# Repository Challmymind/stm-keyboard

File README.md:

First iteration of my 30% keyboard PCB. </br>
Newest board with fixes [here](https://github.com/Challmymind/anvil_pcb).

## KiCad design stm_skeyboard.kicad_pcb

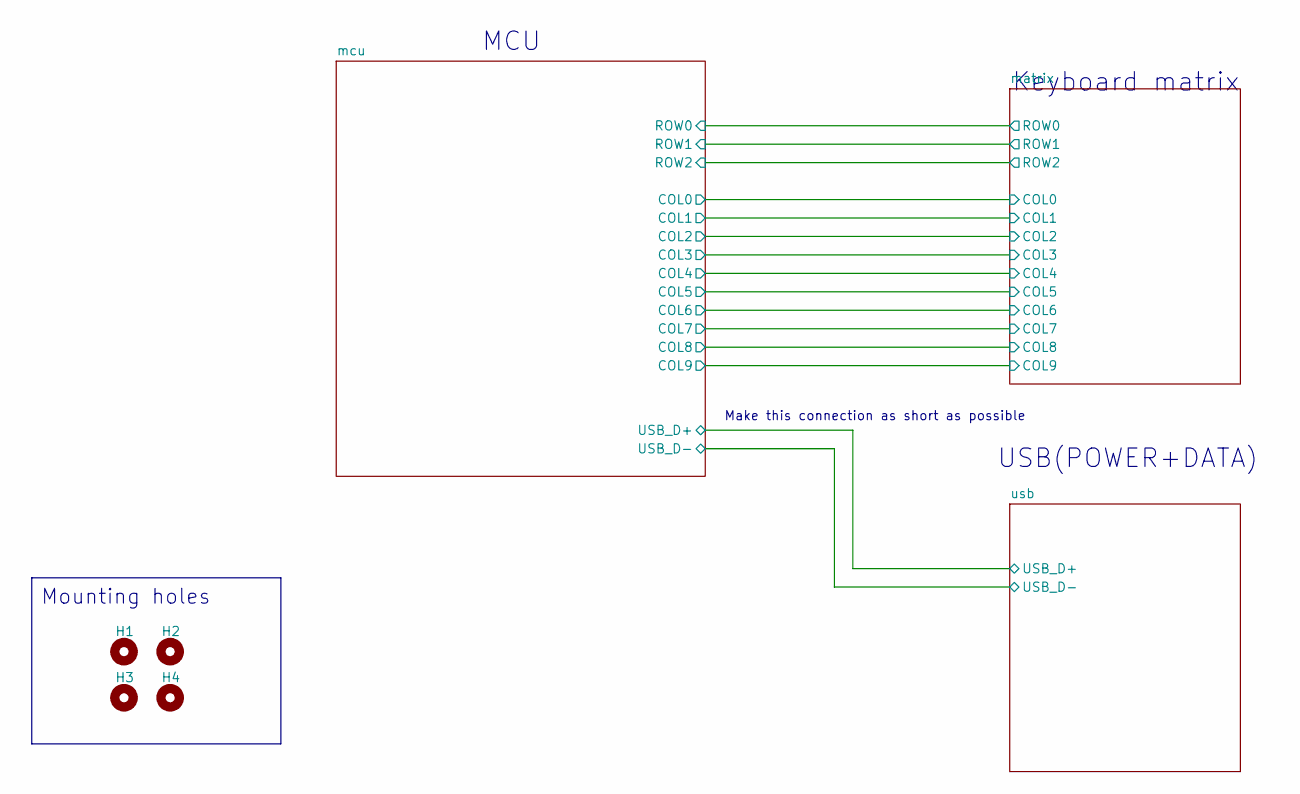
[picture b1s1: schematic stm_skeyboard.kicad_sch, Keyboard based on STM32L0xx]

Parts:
H1, H2, H3, H4: MountingHole; MountingHole_2.1mm

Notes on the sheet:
MCU
Keyboard matrix
Make this connection as short as possible
Mounting holes
USB(POWER+DATA)

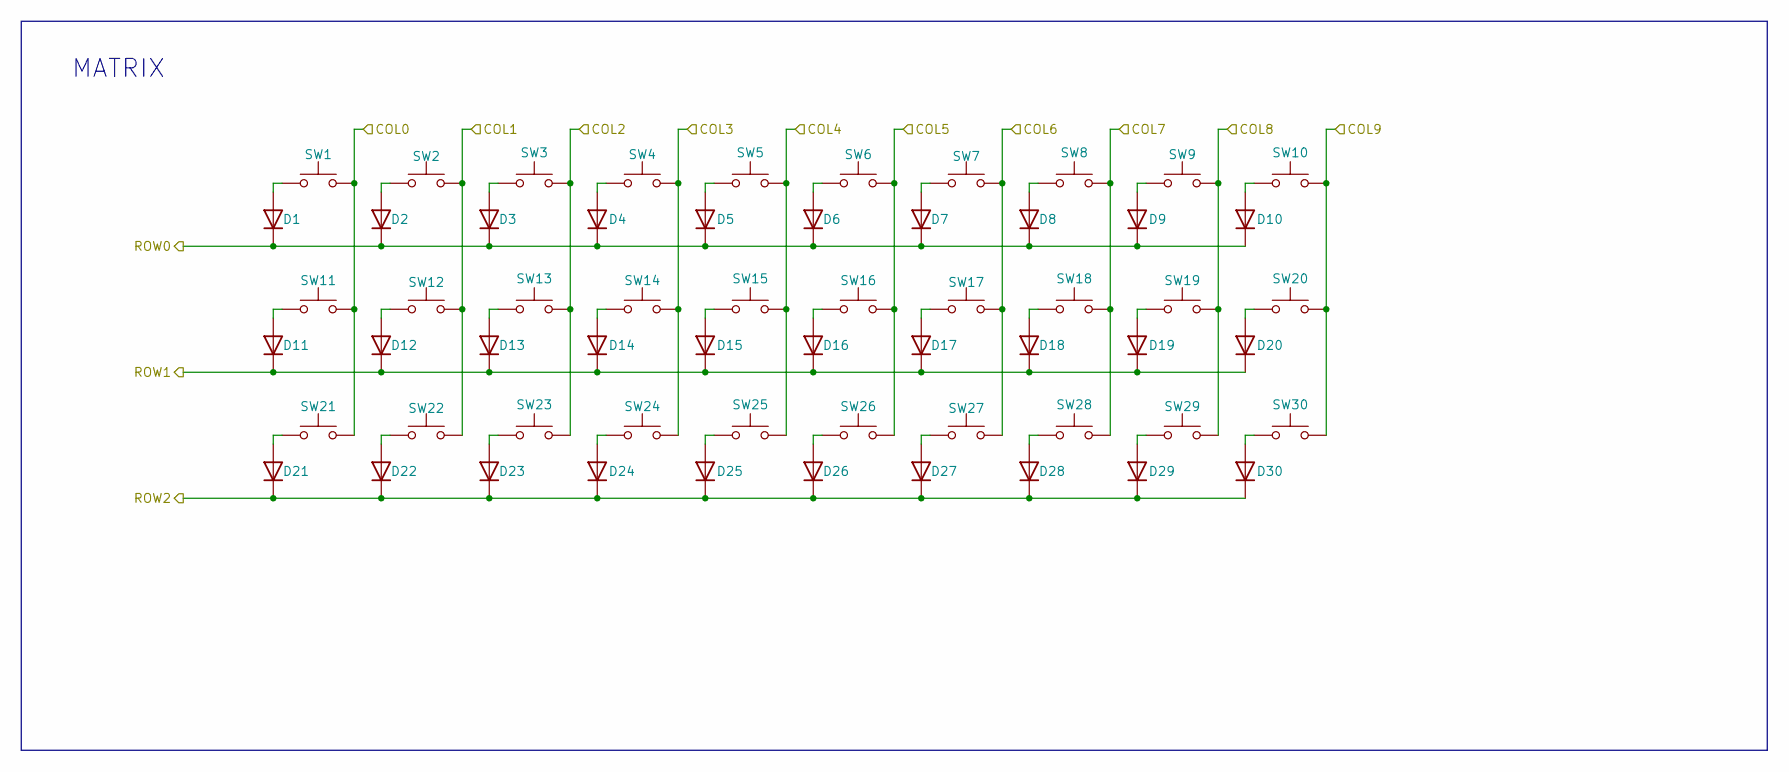
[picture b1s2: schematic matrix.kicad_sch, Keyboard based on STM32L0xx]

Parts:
D1, D2, D3, D4, D5, D6, D7, D8, D9, D10, D11, D12, D13, D14, D15, D16, D17, D18, D19, D20, D21, D22, D23, D24, D25, D26, D27, D28, D29, D30: D; D_SOD-123
SW1, SW2, SW3, SW4, SW5, SW6, SW7, SW8, SW9, SW10, SW11, SW12, SW13, SW14, SW15, SW16, SW17, SW18, SW19, SW20, SW21, SW22, SW23, SW24, SW25, SW26, SW27, SW28, SW29, SW30: SW_Push; SW_Cherry_MX_1.00u_PCB_no_support_stems

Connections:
/matrix/COL0: SW1.2, SW11.2, SW21.2; also elsewhere on the board
/matrix/COL1: SW2.2, SW12.2, SW22.2; also elsewhere on the board
/matrix/COL2: SW3.2, SW13.2, SW23.2; also elsewhere on the board
/matrix/COL3: SW4.2, SW14.2, SW24.2; also elsewhere on the board
/matrix/COL4: SW5.2, SW15.2, SW25.2; also elsewhere on the board
/matrix/COL5: SW6.2, SW16.2, SW26.2; also elsewhere on the board
/matrix/COL6: SW7.2, SW17.2, SW27.2; also elsewhere on the board
/matrix/COL7: SW8.2, SW18.2, SW28.2; also elsewhere on the board
/matrix/COL8: SW9.2, SW19.2, SW29.2; also elsewhere on the board
/matrix/COL9: SW10.2, SW20.2, SW30.2; also elsewhere on the board
/matrix/ROW0: D1.1 (K), D2.1 (K), D3.1 (K), D4.1 (K), D5.1 (K), D6.1 (K), D7.1 (K), D8.1 (K), D9.1 (K), D10.1 (K); also elsewhere on the board
/matrix/ROW1: D11.1 (K), D12.1 (K), D13.1 (K), D14.1 (K), D15.1 (K), D16.1 (K), D17.1 (K), D18.1 (K), D19.1 (K), D20.1 (K); also elsewhere on the board
/matrix/ROW2: D21.1 (K), D22.1 (K), D23.1 (K), D24.1 (K), D25.1 (K), D26.1 (K), D27.1 (K), D28.1 (K), D29.1 (K), D30.1 (K); also elsewhere on the board
unnamed: D1.2 (A), SW1.1
unnamed: D2.2 (A), SW2.1
unnamed: D3.2 (A), SW3.1
unnamed: D4.2 (A), SW4.1
unnamed: D5.2 (A), SW5.1
unnamed: D6.2 (A), SW6.1
unnamed: D7.2 (A), SW7.1
unnamed: D8.2 (A), SW8.1
unnamed: D9.2 (A), SW9.1
unnamed: D10.2 (A), SW10.1
unnamed: D11.2 (A), SW11.1
unnamed: D12.2 (A), SW12.1
unnamed: D13.2 (A), SW13.1
unnamed: D14.2 (A), SW14.1
unnamed: D15.2 (A), SW15.1
unnamed: D16.2 (A), SW16.1
unnamed: D17.2 (A), SW17.1
unnamed: D18.2 (A), SW18.1
unnamed: D19.2 (A), SW19.1
unnamed: D20.2 (A), SW20.1
unnamed: D21.2 (A), SW21.1
unnamed: D22.2 (A), SW22.1
unnamed: D23.2 (A), SW23.1
unnamed: D24.2 (A), SW24.1
unnamed: D25.2 (A), SW25.1
unnamed: D26.2 (A), SW26.1
unnamed: D27.2 (A), SW27.1
unnamed: D28.2 (A), SW28.1
unnamed: D29.2 (A), SW29.1
unnamed: D30.2 (A), SW30.1

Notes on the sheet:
MATRIX

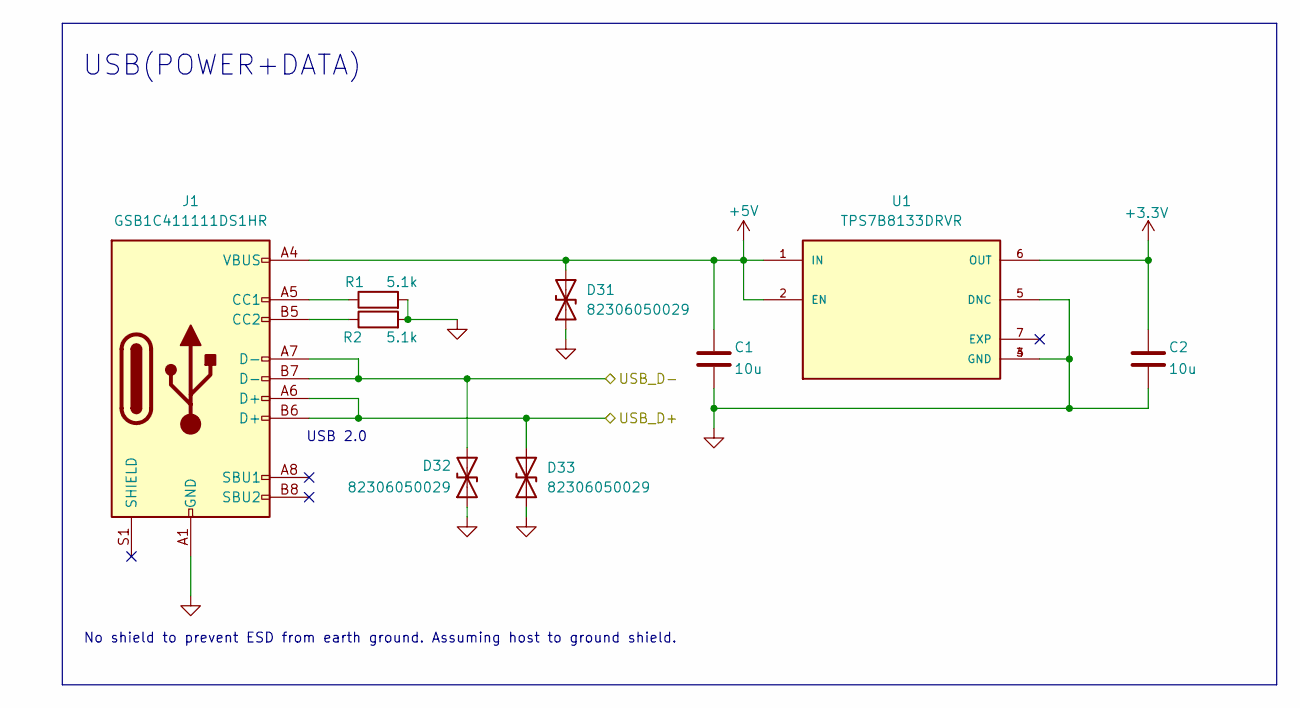
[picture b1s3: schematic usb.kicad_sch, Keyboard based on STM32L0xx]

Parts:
C1, C2: 10u; C_0603_1608Metric
D31, D32, D33: 82306050029; D_0603_1608Metric
J1: GSB1C411111DS1HR; AMPHENOL_GSB1C411111DS1HR
R1, R2: 5.1k; R_0402_1005Metric
U1: TPS7B8133DRVR; SON65P200X200X80-7N; PARTREV April 2020

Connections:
+3.3V: C2.1, U1.6 (OUT); also elsewhere on the board
+5V: C1.1, D31.2 (A2), J1.A4 (VBUS), J1.A4B9, J1.A9 (VBUS), J1.B4 (VBUS), J1.B4A9, J1.B9 (VBUS), U1.1 (IN), U1.2 (EN)
/mcu/USB_D+: D33.2 (A2), J1.A6 (D+), J1.B6 (D+); also elsewhere on the board
/mcu/USB_D-: D32.2 (A2), J1.A7 (D-), J1.B7 (D-); also elsewhere on the board
GND: C1.2, C2.2, D31.1 (A1), D32.1 (A1), D33.1 (A1), J1.A1 (GND), J1.A1B12, J1.A12 (GND), J1.B1 (GND), J1.B1A12, J1.B12 (GND), R1.2, R2.2, U1.3 (GND), U1.4 (GND), U1.5 (DNC); also elsewhere on the board
unnamed: J1.A5 (CC1), R1.1
unnamed: J1.B5 (CC2), R2.1

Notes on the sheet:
USB(POWER+DATA)
USB 2.0
No shield to prevent ESD from earth ground. Assuming host to ground shield.

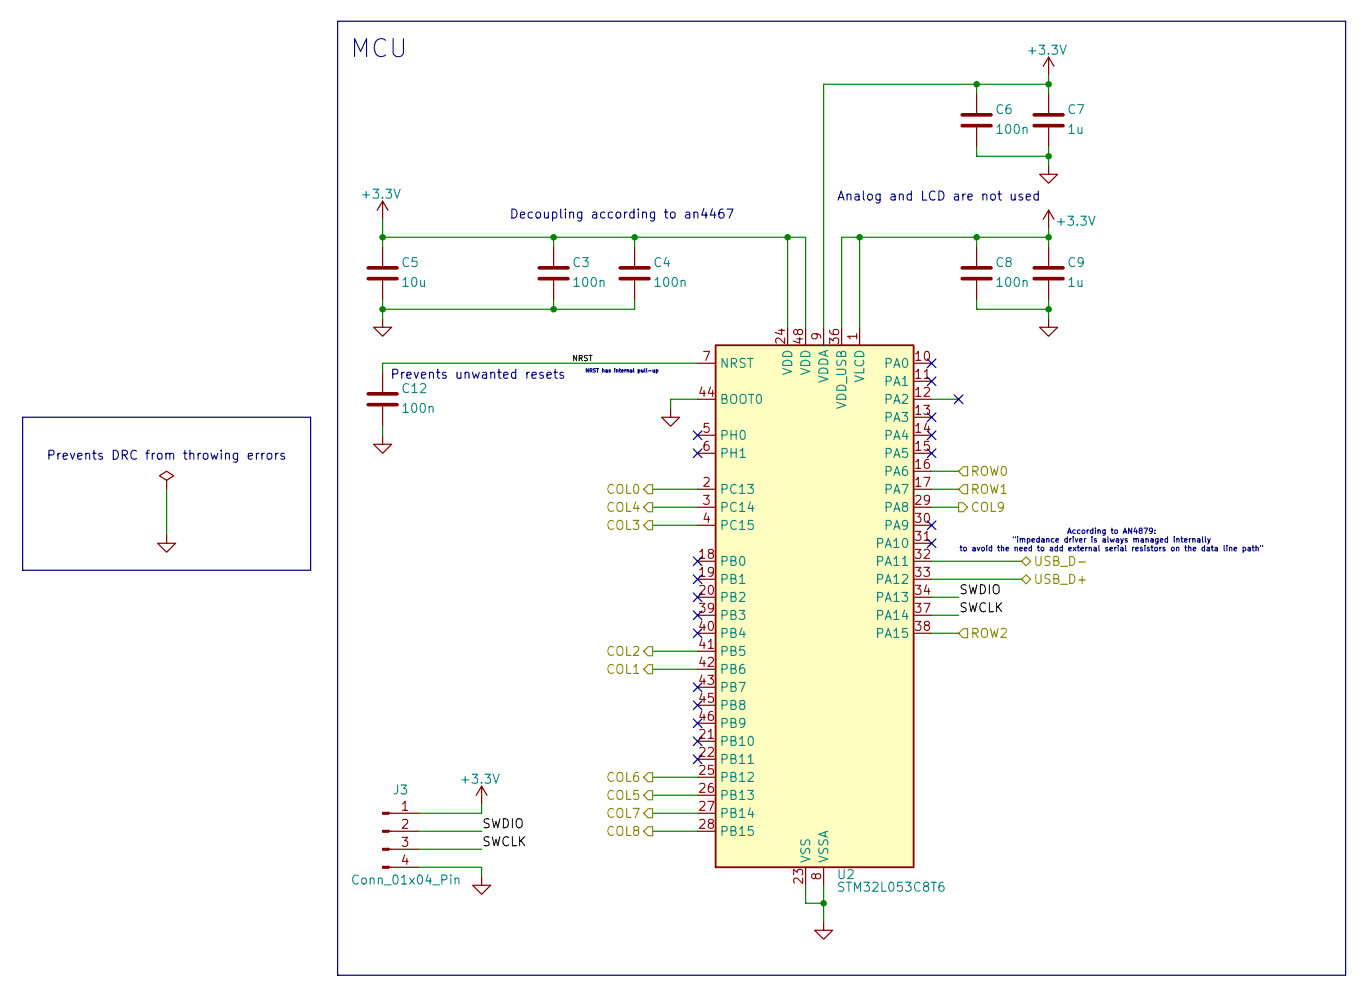
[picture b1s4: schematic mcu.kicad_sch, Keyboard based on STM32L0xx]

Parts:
C3, C4, C6, C8, C12: 100n; C_0402_1005Metric
C5: 10u; C_0603_1608Metric
C7, C9: 1u; C_0402_1005Metric
J3: Conn_01x04_Pin; PinHeader_1x04_P2.54mm_Vertical
U2: STM32L053C8T6; LQFP-48_7x7mm_P0.5mm

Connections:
+3.3V: C3.1, C4.1, C5.1, C6.1, C7.1, C8.1, C9.1, J3.1, U2.1 (VLCD), U2.9 (VDDA), U2.24 (VDD), U2.36 (VDD_USB), U2.48 (VDD); also elsewhere on the board
/matrix/COL0: U2.2 (PC13); also elsewhere on the board
/matrix/COL1: U2.42 (PB6); also elsewhere on the board
/matrix/COL2: U2.41 (PB5); also elsewhere on the board
/matrix/COL3: U2.4 (PC15); also elsewhere on the board
/matrix/COL4: U2.3 (PC14); also elsewhere on the board
/matrix/COL5: U2.26 (PB13); also elsewhere on the board
/matrix/COL6: U2.25 (PB12); also elsewhere on the board
/matrix/COL7: U2.27 (PB14); also elsewhere on the board
/matrix/COL8: U2.28 (PB15); also elsewhere on the board
/matrix/COL9: U2.29 (PA8); also elsewhere on the board
/matrix/ROW0: U2.16 (PA6); also elsewhere on the board
/matrix/ROW1: U2.17 (PA7); also elsewhere on the board
/matrix/ROW2: U2.38 (PA15); also elsewhere on the board
/mcu/NRST: C12.1, U2.7 (NRST)
/mcu/SWCLK: J3.3, U2.37 (PA14)
/mcu/SWDIO: J3.2, U2.34 (PA13)
/mcu/USB_D+: U2.33 (PA12); also elsewhere on the board
/mcu/USB_D-: U2.32 (PA11); also elsewhere on the board
GND: C3.2, C4.2, C5.2, C6.2, C7.2, C8.2, C9.2, C12.2, J3.4, U2.8 (VSSA), U2.23 (VSS), U2.35 (VSS), U2.44 (BOOT0), U2.47 (VSS); also elsewhere on the board

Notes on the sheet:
Decoupling according to an4467
Analog and LCD are not used
Prevents unwanted resets
Prevents DRC from throwing errors
According to AN4879: "impedance driver is always managed internally to avoid the need to add external serial resistors on the data line path"
NRST has internal pull-up
MCU

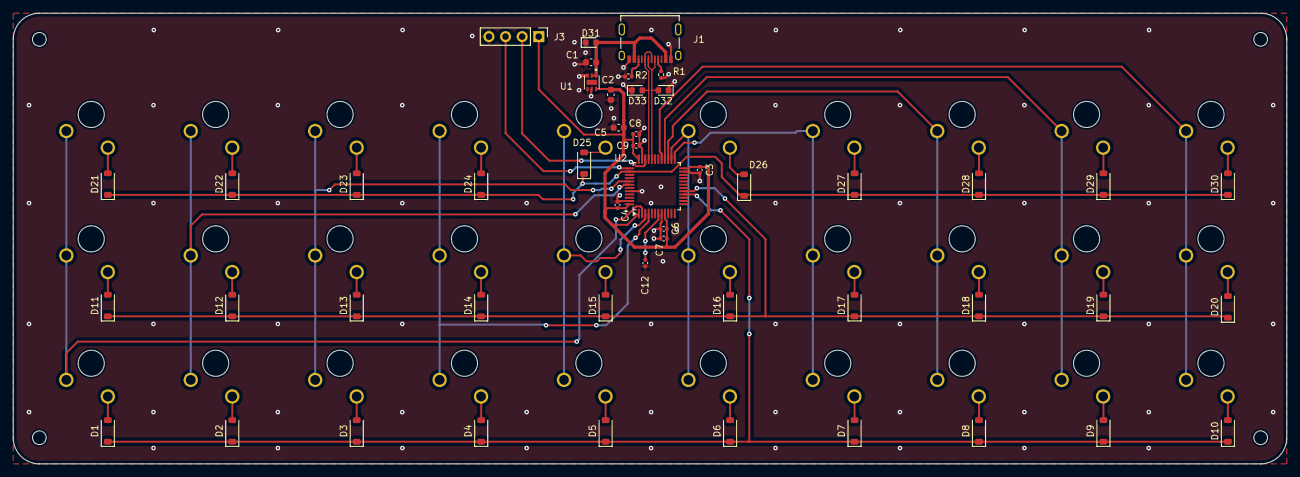
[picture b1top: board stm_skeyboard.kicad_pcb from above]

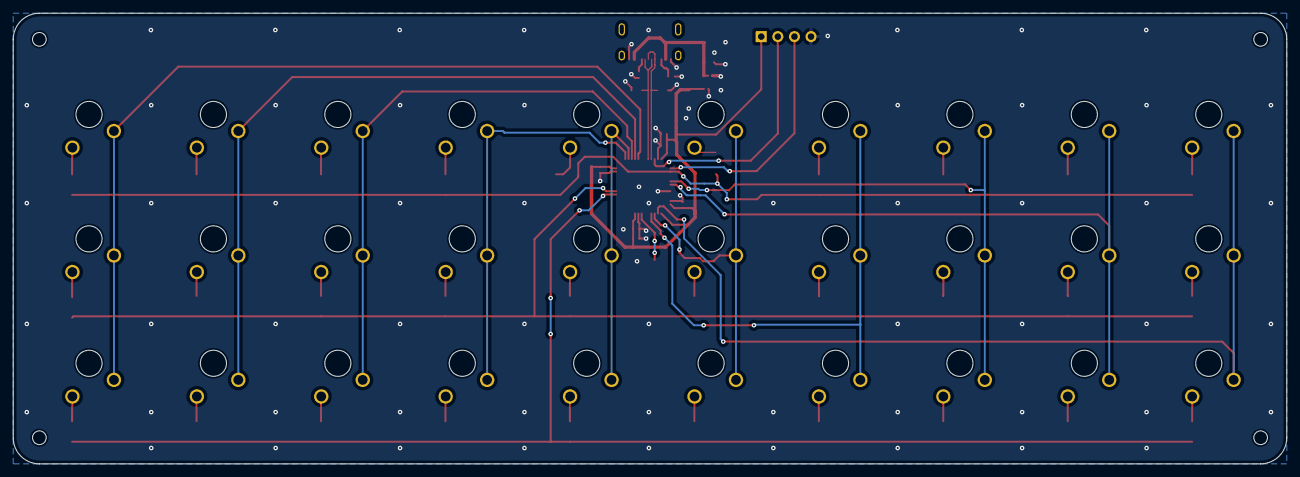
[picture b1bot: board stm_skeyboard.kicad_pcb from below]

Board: 2 copper layers, 195.0 x 69.0 mm, 83 parts (30 on the bottom side), 53 nets.

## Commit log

2024-04-28 initial schematics
2024-04-28 adjust paths for kicanvas
2024-04-28 moved usb to another sheet, cleared ERC violations
2024-04-29 completed 0.1 schematic design
2024-05-03 switched to bigger matrix, adjusted mcu pins, started pcb layout
2024-05-06 added 3d models, completed 0.1
2024-05-06 added routing
2024-05-13 repair decoupling and fill front layer
2024-05-27 re-done whole pcb
2024-06-08 added ESD protection, re-wired matrix
